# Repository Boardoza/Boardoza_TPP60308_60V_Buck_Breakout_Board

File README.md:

# Boardoza TPP60308 60V Buck Breakout Board

The **Boardoza TPP60308 Buck Breakout Board** is a **step-down DC-DC converter** board based on the TPP60308 regulator IC. Designed for efficient power conversion, the board supports pulse-skipping operation for improved efficiency at light loads and provides flexible switching-frequency control. It also includes useful power-management features such as soft-start and protection against overcurrent and excessive temperature.

The board operates from a wide 5V - 60V input range and provides a regulated 5V output with 3A continuous output current, supporting loads up to 3.5A. Its **RT/CLK (Resistor-Timing / Clock) pin allows the switching frequency to be adjusted** from 100kHz to 2.5MHz using an external resistor. The same pin can also receive an external clock signal, allowing the converter to synchronize its switching frequency using its **integrated PLL (Phase-Locked Loop)**. These capabilities make the board suitable for **embedded systems, industrial power conversion, control electronics, and applications requiring a stable 5V supply from 60V DC sources**.

|Front Side|Back Side|
|:---:|:---:|
|||

---

## Key Features

- **Wide-Input Buck Conversion:** Converts 60V DC supplies to a regulated 5V output for embedded and industrial electronics.
- **Light-Load Efficiency:** Pulse-skipping operation reduces switching losses when the connected load requires little power.
- **Flexible Frequency Control:** Adjustable switching frequency enables designs to balance efficiency, component size, and electromagnetic interference.
- **External Clock Synchronization:** Integrated PLL allows the converter switching frequency to synchronize with an external clock source.
- **Integrated Protection:** Thermal shutdown, overcurrent protection, and undervoltage lockout (UVLO) help protect the converter during abnormal operating conditions.
- **Controlled Power-Up:** Adjustable soft-start helps reduce inrush current during converter startup.

---

## Technical Specifications

**Model:** TPP60308   
**Manufacturer:** Boardoza  
**Manufacturer IC:** 3PEAK  
**Input Voltage:** 5V - 60V  
**Functions:** Step-Down DC-DC Voltage Conversion  
**Output Voltage:** 5V  
**Continuous Output Current:** 3A  
**Maximum IC Output Current:** 3.5A  
**Switching Frequency:** 100kHz - 2.5MHz  
**External Clock Frequency:** 160kHz - 2.3MHz  
**Internal Voltage Reference:** 0.8V, 1.5%  
**Operating Quiescent Current:** 160µA  
**Shutdown Current:** 2.25µA  
**Operating Temperature:** -40°C to +125°C  
**Board Dimensions:** 60mm x 20mm

---

## Board Pinout

### ( J1 ) Power and Converter Control Pins

| Pin Number | Pin Name | Description |
| :---: | :---: | --- |
| 1 | VCC | Power Supply Input (5V - 60V) |
| 2 | EN | Active-High Device Enable Pin with Internal Pull-Up Current Source |
| 3 | CLK | RT/CLK Frequency-Setting and External Clock Synchronization Input |
| 4 | GND | Ground |

### ( J2 ) Regulated Power Output

| Pin Number | Pin Name | Description |
| :---: | :---: | --- |
| 1 | VOUT | Regulated 5V DC Output |
| 2 | GND | Ground |

>Note: The RT/CLK pin can be used in two ways. An external resistor can set the switching frequency from 100kHz to 2.5MHz, or an external clock signal can synchronize the converter through its integrated PLL (Phase-Locked Loop). For external clock synchronization, the supported input frequency is 160kHz - 2.3MHz, with HIGH > 2V, LOW < 0.5V, and a minimum pulse width of 15ns.

---

## Board Dimensions

---

## Step Files

[Boardoza TPP60308.step](./assets/TPP60308%20Step.step)

---

## Sensor Datasheet

[TPP60308 Datasheet.pdf](./assets/TPP60308%20Datasheet.pdf)

---

## Version History

- V1.0.0 - Initial Release

---

## Support

- If you have any questions or need support, please contact <support@boardoza.com>

---

## **License**
### **Hardware Design**

[![CC BY-SA 4.0][cc-by-sa-shield]][cc-by-sa]

All hardware design files are licensed under [Creative Commons Attribution-ShareAlike 4.0 International License][cc-by-sa].

[cc-by-sa]: http://creativecommons.org/licenses/by-sa/4.0/
[cc-by-sa-shield]: https://img.shields.io/badge/License-CC%20BY--SA%204.0-lightgrey.svg

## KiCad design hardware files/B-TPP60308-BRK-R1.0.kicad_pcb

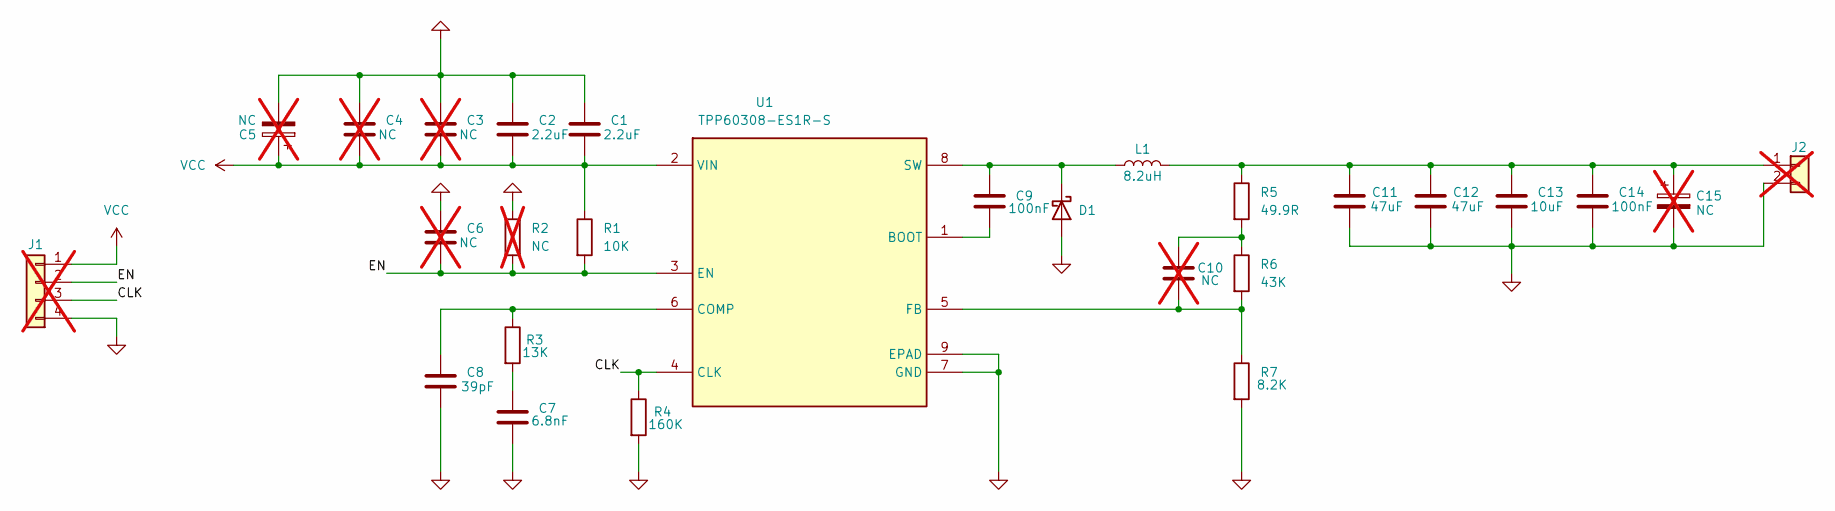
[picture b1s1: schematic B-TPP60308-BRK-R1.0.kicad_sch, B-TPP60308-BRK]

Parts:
C1, C2: 2.2uF; C_1206_3216Metric; MPN CL31B225KCHSNNE
C3, C4, C6, C10: NC; C_0603_1608Metric; not fitted
C5, C15: NC; CP_Elec_4x5.4; MPN JCS1H010M040054; not fitted
C7: 6.8nF; C_0603_1608Metric; MPN CL10B682KB8NNNC
C8: 39pF; C_0603_1608Metric; MPN MCF03JTN500390
C9, C14: 100nF; C_0603_1608Metric; MPN CC0603KRX7R9BB104
C11, C12: 47uF; C_1210_3225Metric; MPN CL32A476KOJNNNE
C13: 10uF; C_0603_1608Metric; MPN GRM188C81C106MA73D
D1: SS8PH10HM3_A/H; SS8PH10HM3_AH; MPN ST STTH802SF
J1: Conn_01x04; 2317-04S_1x04_P2.50mm_Vertical; MPN L-KLS1-2.50-04-SB; not fitted
J2: Conn_01x02; 2317-02S_1x02_P2.50mm_Vertical; MPN L-KLS1-2.50-02-SB; not fitted
L1: 8.2uH; L_Bourns_SRP1038C_10.0x10.0mm; MPN SDI105R-8R2M
R1: 10K; R_0603_1608Metric; MPN CRT03F7E1002
R2: NC; R_0603_1608Metric; not fitted
R3: 13K; R_0805_2012Metric; MPN 0805S8F1302T5E
R4: 160K; R_0603_1608Metric; MPN 0603SAF1603T5E
R5: 49.9R; R_0603_1608Metric; MPN 0603SAF499JT5E
R6: 43K; R_0603_1608Metric; MPN 0603SAF4302T5E
R7: 8.2K; R_0603_1608Metric; MPN 0603SAF8201T5E
U1: TPP60308-ES1R-S; SOIC127P600X170-9N; Manufacturer_Part_Number TPP60308-ES1R-S

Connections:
/CLK: J1.3, R4.1, U1.4 (CLK)
/EN: C6.2, J1.2, R1.2, R2.2, U1.3 (EN)
GND: C1.1, C2.1, C3.1, C4.1, C5.2, C6.1, C7.2, C8.2, C11.2, C12.2, C13.2, C14.2, C15.2, D1.1 (A), D1.2 (A), J1.4, J2.2, R2.1, R4.2, R7.2, U1.7 (GND), U1.9 (EPAD)
unnamed: C7.1, R3.2
unnamed: C10.1, R5.2, R6.1
unnamed: C9.1, D1.3 (K), L1.1, U1.8 (SW)
unnamed: C11.1, C12.1, C13.1, C14.1, C15.1, J2.1, L1.2, R5.1
unnamed: C9.2, U1.1 (BOOT)
unnamed: C8.1, R3.1, U1.6 (COMP)
unnamed: C10.2, R6.2, R7.1, U1.5 (FB)
VCC: C1.2, C2.2, C3.2, C4.2, C5.1, J1.1, R1.1, U1.2 (VIN)

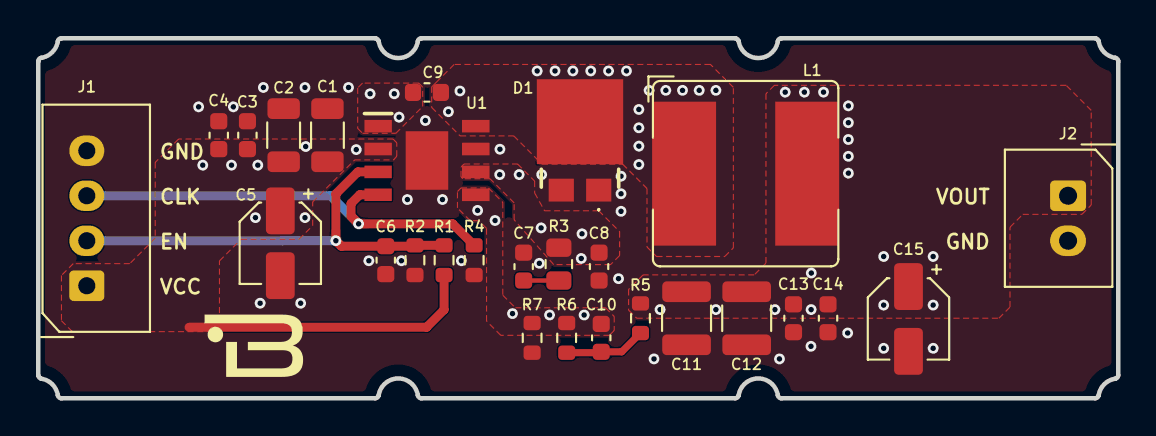
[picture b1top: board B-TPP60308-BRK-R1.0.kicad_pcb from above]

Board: 2 copper layers, 60.0 x 20.0 mm, 27 parts (0 on the bottom side), 11 nets.
